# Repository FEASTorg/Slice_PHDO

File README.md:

# pH and Dissolved Oxygen Atlas Sci Slice

pH and DO sensor carrier slice for BREAD [for Atlas Scientific Ezo sensors].

## Introduction

[Short introduction on the project.]

## Usage

[Explain how to use the project. Include examples and screenshots if applicable.]

## Documentation

Please refer to the [docs](/docs) for more info.

---

<div align="center">
  
</div>

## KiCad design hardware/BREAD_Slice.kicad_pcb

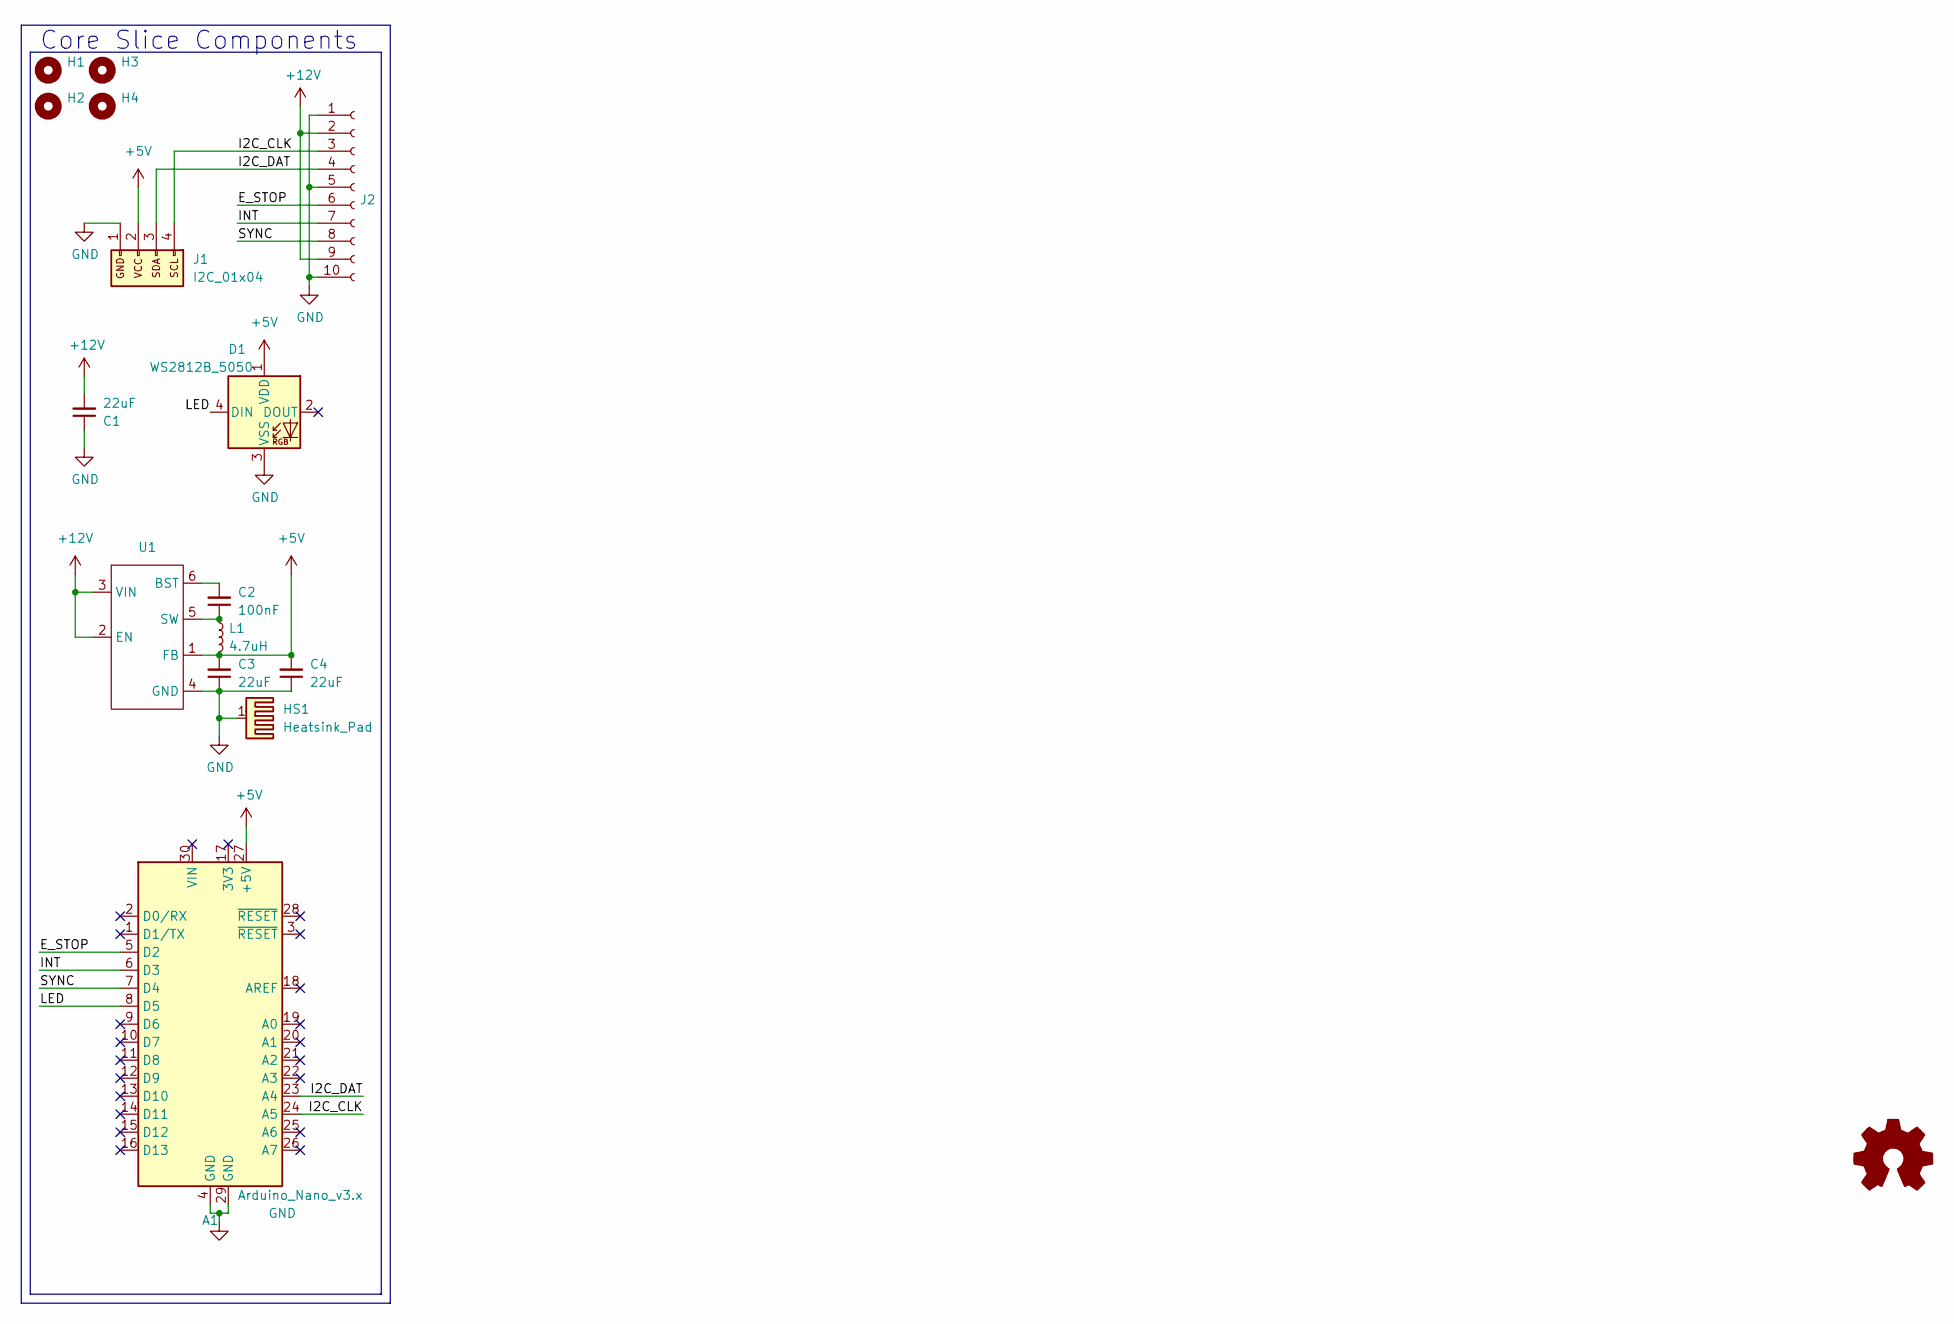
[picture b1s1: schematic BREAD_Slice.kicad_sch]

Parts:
A1: Arduino_Nano_v3.x; Arduino_Nano
C1, C3, C4: 22uF; C_1206_3216Metric
C2: 100nF; C_1206_3216Metric
D1: WS2812B_5050; WS2812-5050-4PIN
H1, H2, H3, H4: MountingHole; MountingHole_5mm
HS1: Heatsink_Pad; Thermal_Pad
J1: I2C_01x04; JST_SH_SM04B-SRSS-TB_1x04-1MP_P1.00mm_Horizontal
J2: Conn_01x10_Female; PinSocket_1x10_P2.54mm_Horizontal
L1: 4.7uH; L_1210_3225Metric
U1: TSOT-23-6

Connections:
+5V: A1.27 (+5V), C3.2, C4.2, D1.1 (VDD), J1.2, L1.2, U1.1 (FB)
+12V: C1.2, J2.2, J2.9, U1.2 (EN), U1.3 (VIN)
/E_STOP: A1.5 (D2), J2.6
/I2C_CLK: A1.24 (A5), J1.4, J2.3
/I2C_DAT: A1.23 (A4), J1.3, J2.4
/INT: A1.6 (D3), J2.7
/LED: A1.8 (D5), D1.4 (DIN)
/SYNC: A1.7 (D4), J2.8
GND: A1.4 (GND), A1.29 (GND), C1.1, C3.1, C4.1, D1.3 (VSS), HS1.1, J1.1, J2.1, J2.5, J2.10, U1.4 (GND)
unnamed: C2.2, U1.6 (BST)
unnamed: C2.1, L1.1, U1.5 (SW)

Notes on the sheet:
Core Slice Components

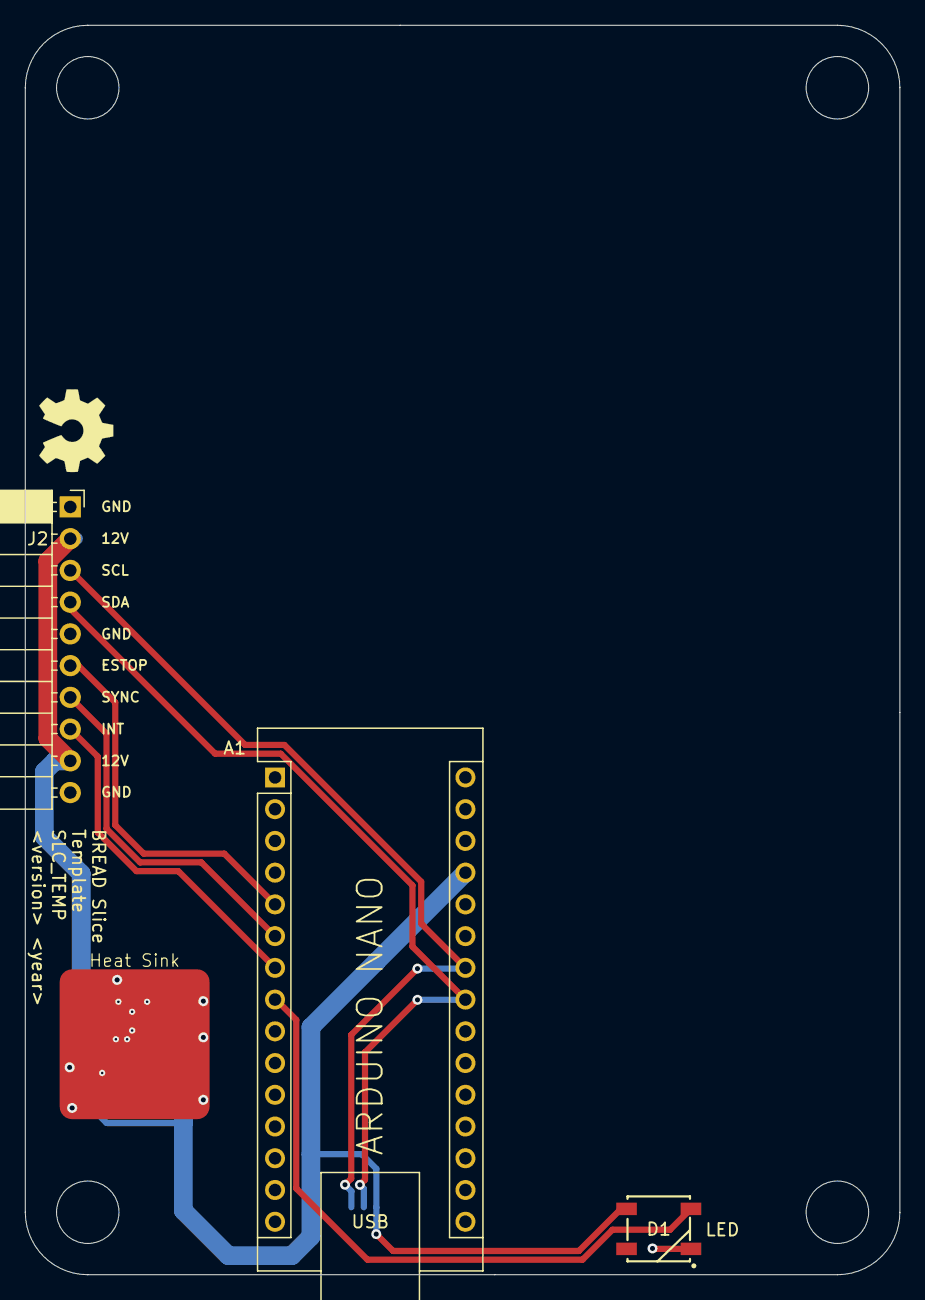
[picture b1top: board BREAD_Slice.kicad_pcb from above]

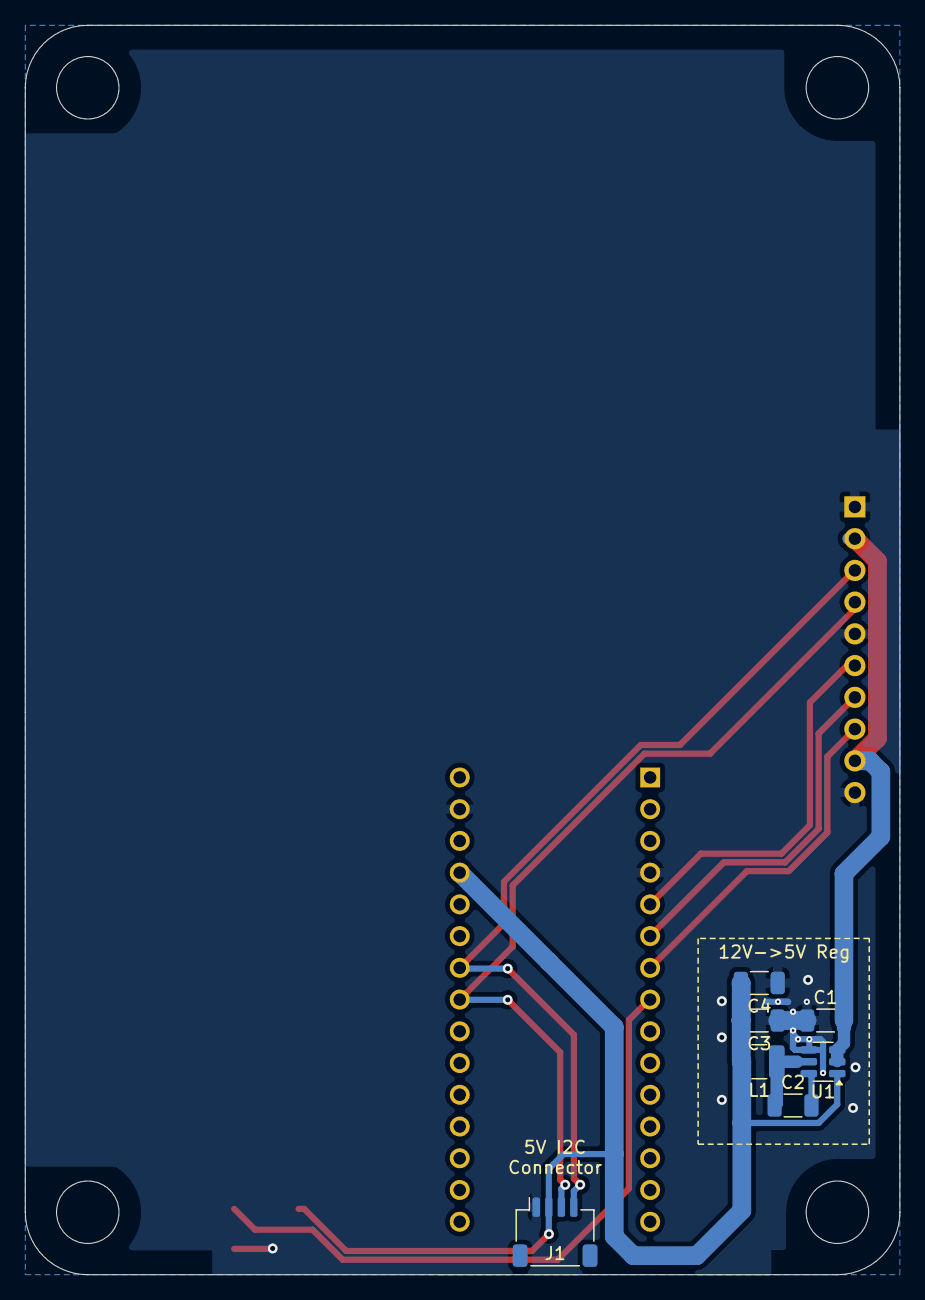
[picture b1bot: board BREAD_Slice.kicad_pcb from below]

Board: 2 copper layers, 70.0 x 100.0 mm, 16 parts (7 on the bottom side), 11 nets.

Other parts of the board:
Logo1: Logo_Open_Hardware_Small; OSHW-Symbol_6.7x6mm_SilkScreen

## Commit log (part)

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2026-05-20 Add slice.yaml manifest (schema v1.0)
2026-05-24 Add KiBot/docs pipeline
2026-05-24 Update TODO with CI findings
2026-05-24 Standardize TODO.md with Pass 1/Pass 2 structure
